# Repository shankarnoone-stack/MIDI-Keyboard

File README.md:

# MIDI-Keyboard
MIDI Keyboard is a small piano-like PCB made with a Waveshare ESP32-S3-ZERO. It uses switches, touch sensors, a rotary encoder, LEDs, and a Bourns Potentiometer.

I designed the schematic and PCB in KiCad, routed the traces, and exported the fabrication files. This is my Week 3 PCB project for Hack Club Half Life.

## What it is

MIDI is designed to be like a piano, with capacitive touch sensores, switches, and a rotary encoder. It responds to touch, and plays sound from the response.

## How?

I started by following the guided MIDI Keypad project as this was really similar to my design.
After, I set up the schematic with the Waveshare ESP32-S3-ZERO, the rotary encoder, switches, bourns potentiometers, and the touch keys.
After this, I routed the traces, and checked it using designs rules checker to make sure that it was ok.
I finally exported the fabrication files and created a BOM based on it.

## Why?
I made it for the week 3 Half Life hackclub challenge, to learn about how to use KiCad and build a PCB and Schematic.

## BOM.csv
I looked towards Aliexpress for my parts, and used JLCPCB for my PCB vendor. For my Bourns Potentiometers, I first thought of aliexpress, but then I realized it was only really found in Digikey.
| Part | What it is used for | Quantity | Price | Vendor |
|---|---|---:|---:|---|
| [Waveshare ESP32-S3-ZERO]| Main microcontroller | 1 |$1.46| Aliexpress|
| [Rotary Encoder]|Knob on PCB | 1 | $1.52 |Amazon|
| [Bourns Potentiometers]| Sliders | 1 | $3.68 | Digikey |
| [SK6812 MINI-E]| LEDs for switches| 1 | $3.61 | Aliexpress |
| [Choc Switches]| Switches | 1 | $3.67 | Aliexpress |
| [PCB Fabrication]| Custom circuit board manufacturing | 1 | $8.61 | JLCPCB |

- **Parts Subtotal:** 22.55
- **Tax & Shipping:** $9.76
- **Total Project Cost:** **$32.31**

## Repository contents

- KiCad source files and fabrication exports
- PCB and Schematic renders
- BOM
- Gerber files

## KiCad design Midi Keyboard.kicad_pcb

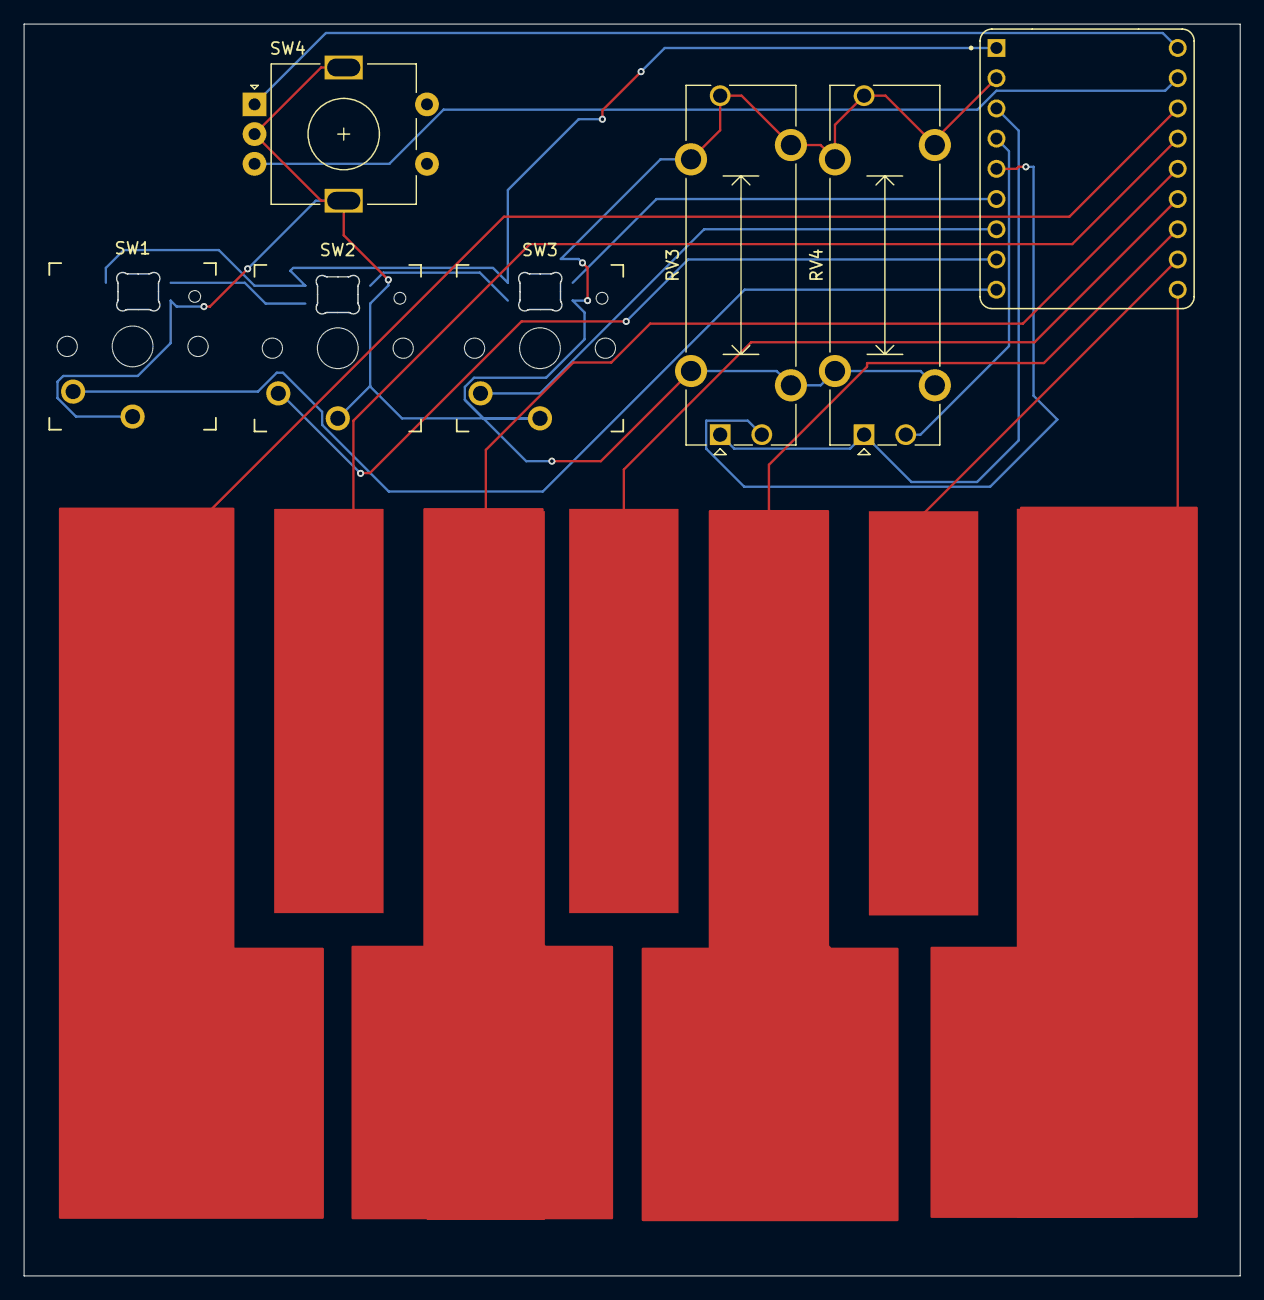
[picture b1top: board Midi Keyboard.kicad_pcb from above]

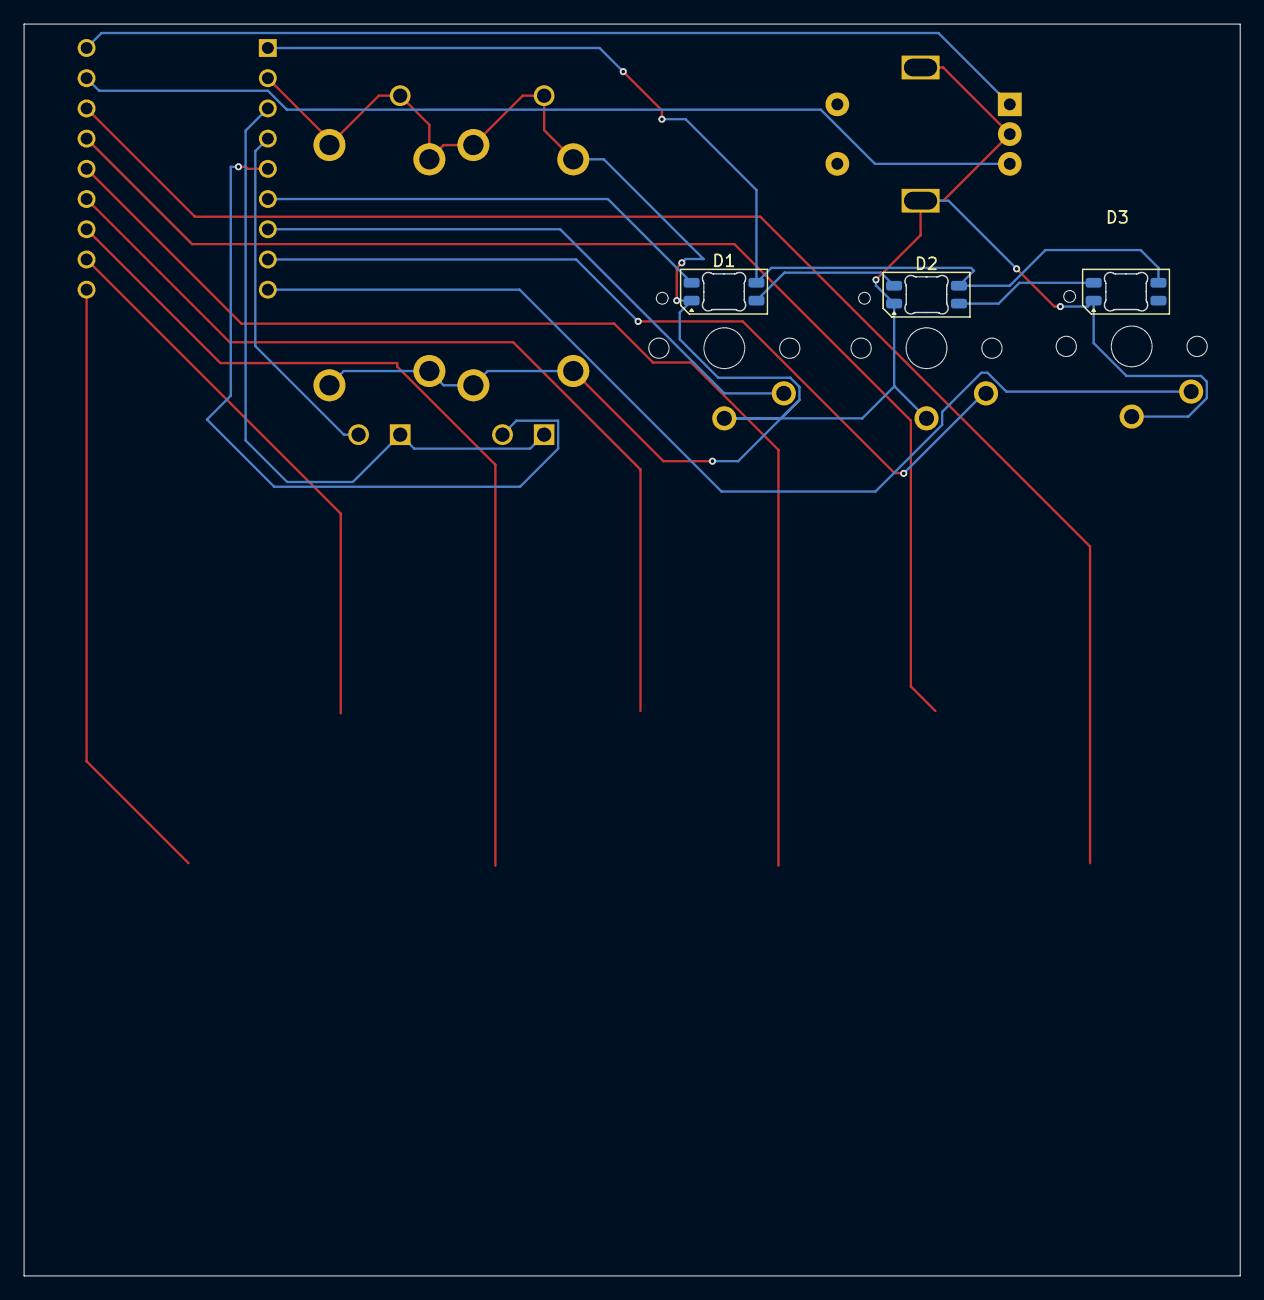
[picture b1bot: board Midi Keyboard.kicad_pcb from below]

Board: 2 copper layers, 102.2 x 105.2 mm, 11 parts (3 on the bottom side), 20 nets.

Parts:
D1, D2, D3: SK6812MINI-E; LED_SK6812MINI-E_3.2x2.8mm_P1.5mm_ReverseMount
J1: Conn_01x07; MIDI Keyboard
RV3, RV4: Slider; Potentiometer_Bourns_PTA1543_Single_Slide
SW1, SW2, SW3: SW_Push; Kailh Choc Low-Profile Switches
SW4: RotaryEncoder_Switch_MP; RotaryEncoder_Alps_EC11E-Switch_Vertical_H20mm
U2: ESP32-S3-ZERO; MODULE_ESP32-S3-ZERO

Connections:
+3V3: RV3.1, RV4.1, U2.3V3 (3V3(OUT))
+5V: D1.3 (VDD), D2.3 (VDD), D3.3 (VDD), U2.5V
/ENC 1 A: SW4.A, U2.TX
/ENC 1 B: SW4.B, U2.RX
/LED: D1.2 (DIN), U2.3 (GP3)
/SLIDE 1: RV3.2, U2.2 (GP2)
/SLIDE 2: RV4.2, U2.1 (GP1)
/SWITCH 1: SW3.2, U2.4 (GP4)
/SWITCH 2: SW2.2, U2.5 (GP5)
/SWITCH 3: SW1.2, U2.6 (GP6)
/TOUCH 1: J1.1, U2.13 (GP13)
/TOUCH 2: J1.2, U2.12 (GP12)
/TOUCH 3: J1.3, U2.11 (GP11)
/TOUCH 4: J1.4, U2.10 (GP10)
/TOUCH 5: J1.5, U2.9 (GP9)
/TOUCH 6: J1.6, U2.8 (GP8)
/TOUCH 7: J1.7, U2.7 (GP7)
GND: D1.1 (VSS), D2.1 (VSS), D3.1 (VSS), RV3.3, RV3.MP (MountPin), RV4.3, RV4.MP (MountPin), SW1.1, SW2.1, SW3.1, SW4.C, SW4.MP, U2.GND
unnamed: D1.4 (DOUT), D2.2 (DIN)
unnamed: D2.4 (DOUT), D3.2 (DIN)
